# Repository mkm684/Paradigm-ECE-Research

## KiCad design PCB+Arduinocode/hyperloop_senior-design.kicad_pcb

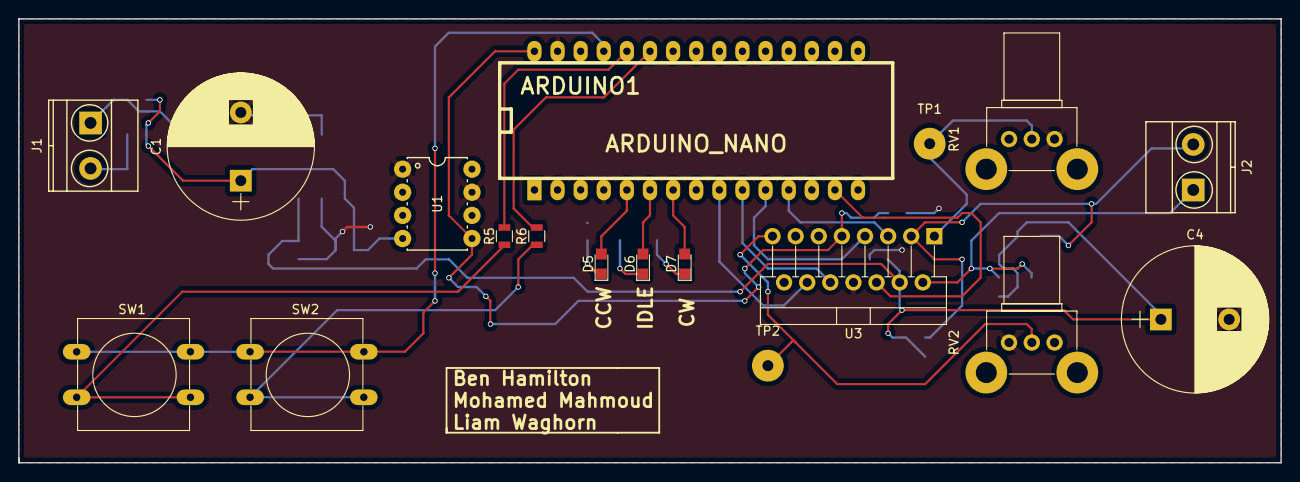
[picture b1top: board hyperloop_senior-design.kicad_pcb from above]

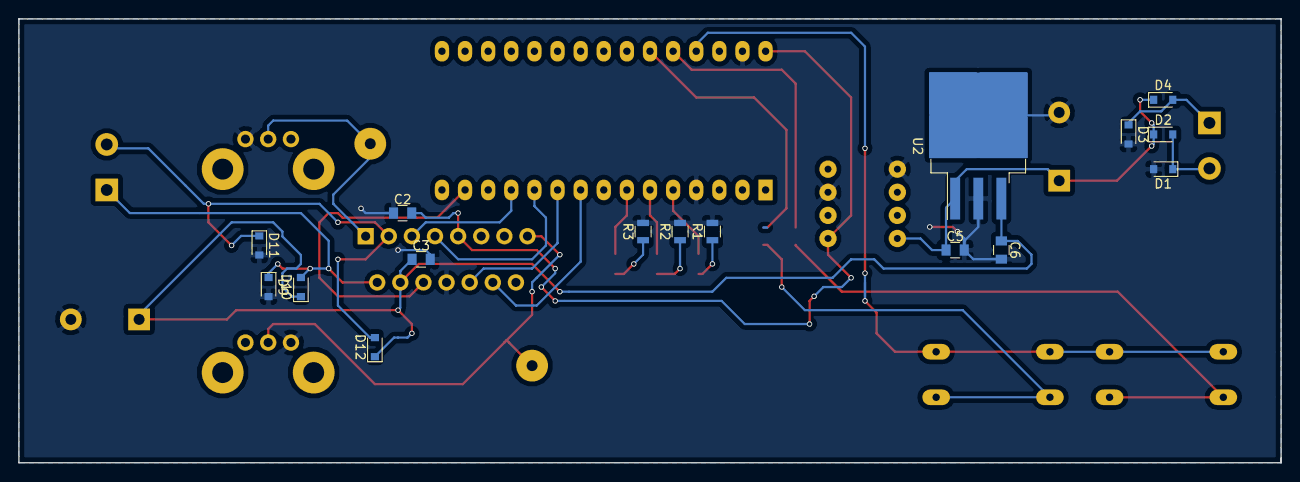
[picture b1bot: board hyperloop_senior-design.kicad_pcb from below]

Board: 2 copper layers, 138.7 x 48.8 mm, 34 parts (16 on the bottom side), 27 nets.

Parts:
ARDUINO1: ARDUINO_NANO; arduino_nano
C1: CP; CP_Radial_D16.0mm_P7.50mm
C2, C3, C5: 0.1uF; C_0805
C4: 47uF; CP_Radial_D16.0mm_P7.50mm
C6: 10uF; C_0805
D1, D2, D3, D4, D9, D10, D11, D12: D; D_0805
D5, D6, D7: LED; LED_0805
J1, J2: Screw_Terminal_01x02; TerminalBlock_Pheonix_MKDS1.5-2pol
R1, R2, R3, R5, R6: R; R_0805
RV1, RV2: POT; Potentiometer_Alps_RK09K_Vertical
SW1, SW2: SW_Push; SW_PUSH-12mm
TP1: S1; SolderWirePad_single_1-2mmDrill
TP2: S2; SolderWirePad_single_1-2mmDrill
U1: RN-2407S; PDIP-8
U2: LM2937IMPX-15/NOPB; TO-263-3_TabPin4
U3: L298N; Multiwatt-15_Vertical_StaggeredType1

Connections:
7V: ARDUINO1.30, C2.2, U1.5, U3.9
15V: C3.1, C4.1, C6.1, D10.1, D12.1, U2.3, U3.4
GND: ARDUINO1.4, ARDUINO1.29, C1.2, C2.1, C3.2, C4.2, C5.2, C6.2, D1.2, D3.2, D9.2, D11.2, R1.2, R2.2, R3.2, RV1.1, RV2.3, U1.1, U1.7, U2.2, U2.4, U3.8
unnamed: ARDUINO1.5, D5.2
unnamed: ARDUINO1.6, D6.2
unnamed: ARDUINO1.7, D7.2
unnamed: ARDUINO1.9, U3.12
unnamed: ARDUINO1.10, U3.10
unnamed: ARDUINO1.11, U3.7
unnamed: ARDUINO1.12, U3.5
unnamed: ARDUINO1.13, U3.11
unnamed: ARDUINO1.14, U3.6
unnamed: ARDUINO1.25, R6.2
unnamed: ARDUINO1.26, R5.2
unnamed: ARDUINO1.27, SW1.1, SW2.1
unnamed: D1.1, D2.2, J1.2
unnamed: D3.1, D4.2, J1.1
unnamed: D5.1, R1.1
unnamed: D6.1, R2.1
unnamed: D7.1, R3.1
unnamed: D9.1, D10.2, J2.1, U3.2
unnamed: D11.1, D12.2, J2.2, U3.3
unnamed: R5.1, SW1.2
unnamed: R6.1, SW2.2
unnamed: RV1.2, TP1.1, U3.1
unnamed: RV2.2, TP2.1, U3.15
Vcc: C1.1, C5.1, D2.1, D4.1, U1.4, U2.1

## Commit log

2017-10-01 moh changes v1
2017-10-02 Create PCB
2017-10-02 Hyperloop schematic/pcb files
2017-10-03 mohamed changes -v2
2017-10-03 Changes to PCB
    -Added board version to silk
    -Added silk button labels
2017-10-03 Added datasheets for ICs
2017-10-03 mohamed changes -v3
2017-10-03 Added MATLAB
2017-10-05 presentation added
